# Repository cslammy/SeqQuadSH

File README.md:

# SeqQuadSH
for details please see this blog post: http://audiodiwhy.blogspot.com/2022/03/sequencial-quad-samplehold.html

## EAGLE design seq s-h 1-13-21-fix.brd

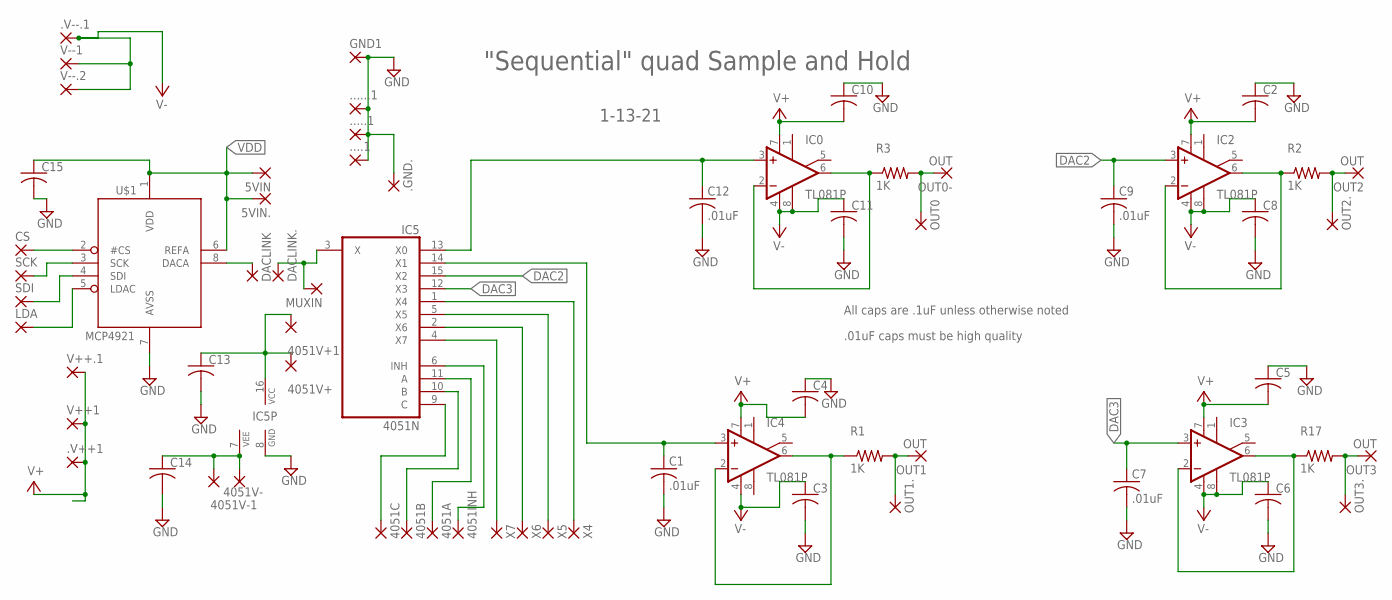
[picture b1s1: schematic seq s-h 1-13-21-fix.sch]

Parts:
5VIN: WIREPAD3,17/1,3; 3,17/1,3@1
5VIN., 4051A, 4051B, 4051C, 4051INH, 4051V+1, 4051V-1, .GND.: WIREPAD1,6/0,9; 1,6/0,9
4051V+, 4051V-, ....1, .....1, ......1, .V--.1: 3,17/1,3
.V++1: 2,54/1,0
C1, C7, C9, C12: .01uF; C050-025X075
C2, C3, C4, C5, C6, C8, C10, C11, C13, C14, C15: C-US025-024X044; C025-024X044
CS: WIREPAD1,6/0,9; 1,6/0,9
DACLINK, DACLINK.: WIREPAD1,6/0,9; 1,6/0,9
GND1: 3,17/1,3
IC0, IC2, IC3, IC4: TL081P; DIL08
IC5: 4051N; DIL16
LDA: WIREPAD1,6/0,9; 1,6/0,9
MUXIN: 3,17/1,3
OUT0, OUT1., OUT2., OUT3.: WIREPAD1,6/0,9; 1,6/0,9
OUT0-, OUT1, OUT2, OUT3: OUT; 3,17/1,3
R1, R2, R3, R17: 1K; 0204/7
SCK: WIREPAD1,6/0,9; 1,6/0,9
SDI: WIREPAD1,6/0,9; 1,6/0,9
U$1: MCP4921; DIL08
V++1, V++.1: 2,54/1,0
V--1, V--.2: 3,17/1,3
X4, X5, X6, X7: WIREPAD1,6/0,9; 1,6/0,9

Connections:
DAC2: C9.1, IC2.3 (+IN), IC5.15 (X2)
DAC3: C7.1, IC3.3 (+IN), IC5.12 (X3)
GND: ....1.1, .....1.1, ......1.1, .GND..1, C1.2, C2.1, C3.2, C4.1, C5.1, C6.2, C7.2, C8.2, C9.2, C10.1, C11.2, C12.2, C13.2, C14.2, C15.2, GND1.1, IC5.8 (GND), U$1.7 (AVSS)
unnamed: OUT1.1, OUT1..1, R1.2
unnamed: DACLINK..1, IC5.3 (X), MUXIN.1
unnamed: C1.1, IC4.3 (+IN), IC5.14 (X1)
unnamed: OUT2.1, OUT2..1, R2.2
unnamed: IC4.2 (-IN), IC4.6 (OUT), R1.1
unnamed: IC2.2 (-IN), IC2.6 (OUT), R2.1
unnamed: CS.1, U$1.2 (#CS)
unnamed: OUT0.1, OUT0-.1, R3.2
unnamed: IC0.2 (-IN), IC0.6 (OUT), R3.1
unnamed: C12.1, IC0.3 (+IN), IC5.13 (X0)
unnamed: SCK.1, U$1.3 (SCK)
unnamed: SDI.1, U$1.4 (SDI)
unnamed: LDA.1, U$1.5 (LDAC)
unnamed: 4051C.1, IC5.9 (C)
unnamed: 4051B.1, IC5.10 (B)
unnamed: 4051A.1, IC5.11 (A)
unnamed: 4051INH.1, IC5.6 (INH)
unnamed: IC3.2 (-IN), IC3.6 (OUT), R17.1
unnamed: OUT3.1, OUT3..1, R17.2
unnamed: IC5.4 (X7), X7.1
unnamed: IC5.2 (X6), X6.1
unnamed: IC5.5 (X5), X5.1
unnamed: IC5.1 (X4), X4.1
unnamed: 4051V+.1, 4051V+1.1, C13.1, IC5.16 (VCC)
unnamed: 4051V-.1, 4051V-1.1, C14.1, IC5.7 (VEE)
unnamed: DACLINK.1, U$1.8 (DACA)
V+: .V++1.1, C2.2, C4.2, C5.2, C10.2, IC0.7 (V+), IC2.7 (V+), IC3.7 (V+), IC4.7 (V+), V++1.1, V++.1.1
V-: .V--.1.1, C3.1, C6.1, C8.1, C11.1, IC0.4 (V-), IC0.8 (OPT), IC2.4 (V-), IC2.8 (OPT), IC3.4 (V-), IC3.8 (OPT), IC4.4 (V-), V--1.1, V--.2.1
VDD: 5VIN.1, 5VIN..1, C15.1, U$1.1 (VDD), U$1.6 (REFA)

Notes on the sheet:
"Sequential" quad Sample and Hold
1-13-21
All caps are .1uF unless otherwise noted
.01uF caps must be high quality

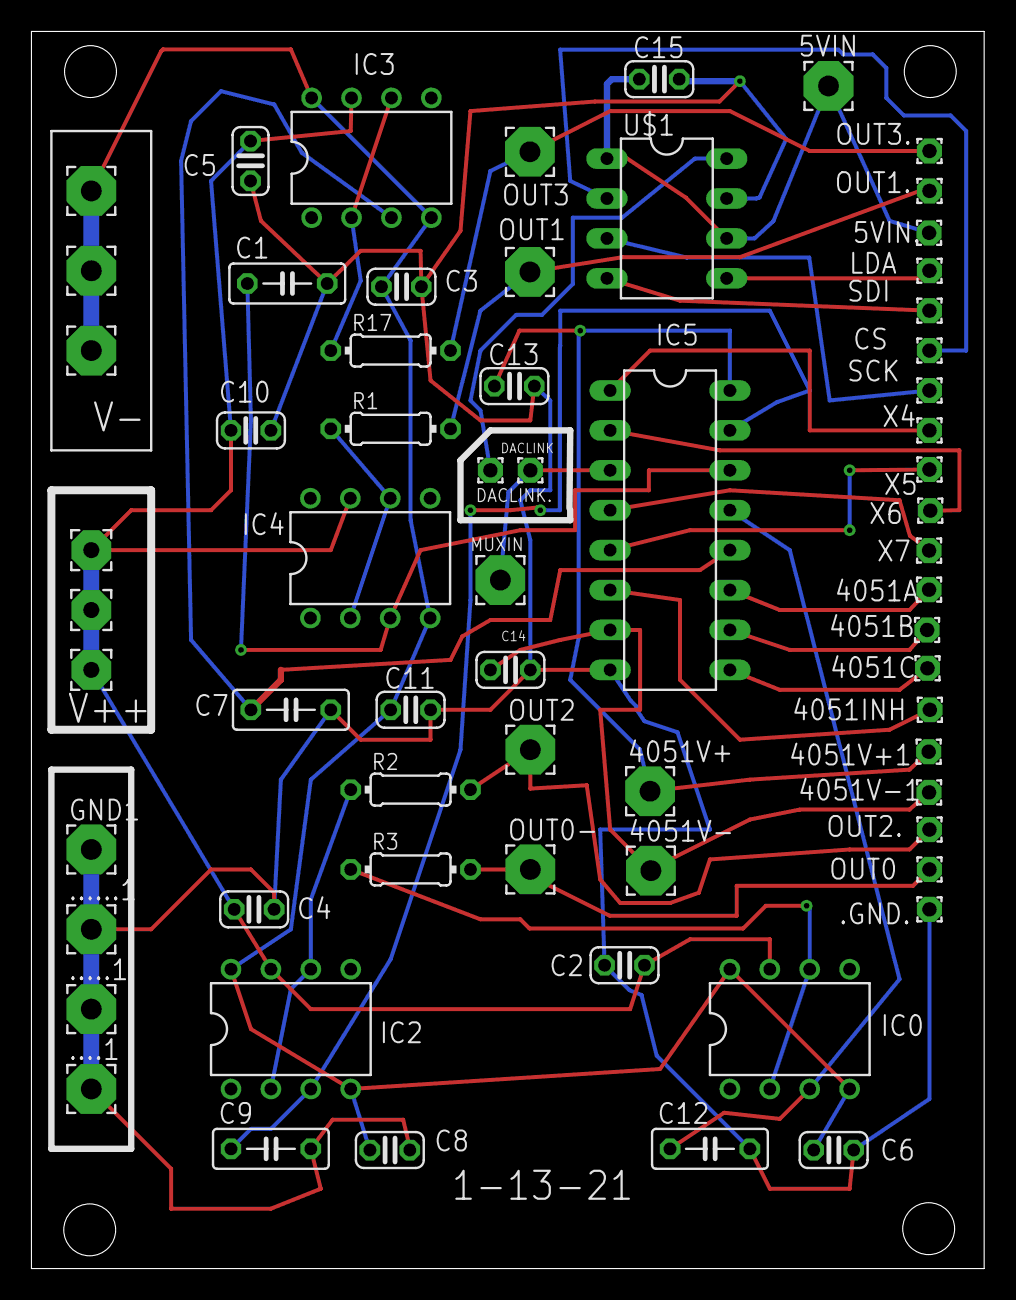
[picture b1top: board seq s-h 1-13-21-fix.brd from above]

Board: 2 copper layers, 60.6 x 78.7 mm, 65 parts (0 on the bottom side), 32 nets.

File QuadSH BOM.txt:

BOM for Seq SH

Part     Value   Device          Package      Description                  POPULARITY SPICEPREFIX
                                  
                     
                                    
                  
C1       .01uF   C-US050-025X075 C050-025X075 CAPACITOR, American symbol   0          C          
C2               C-US025-024X044 C025-024X044 CAPACITOR, American symbol   17         C          
C3               C-US025-024X044 C025-024X044 CAPACITOR, American symbol   17         C          
C4               C-US025-024X044 C025-024X044 CAPACITOR, American symbol   17         C          
C5               C-US025-024X044 C025-024X044 CAPACITOR, American symbol   17         C          
C6               C-US025-024X044 C025-024X044 CAPACITOR, American symbol   17         C          
C7       .01uF   C-US050-025X075 C050-025X075 CAPACITOR, American symbol   0          C          
C8               C-US025-024X044 C025-024X044 CAPACITOR, American symbol   17         C          
C9       .01uF   C-US050-025X075 C050-025X075 CAPACITOR, American symbol   0          C          
C10              C-US025-024X044 C025-024X044 CAPACITOR, American symbol   17         C          
C11              C-US025-024X044 C025-024X044 CAPACITOR, American symbol   17         C          
C12      .01uF   C-US050-025X075 C050-025X075 CAPACITOR, American symbol   0          C          
C13              C-US025-024X044 C025-024X044 CAPACITOR, American symbol   17         C          
C14              C-US025-024X044 C025-024X044 CAPACITOR, American symbol   17         C          
C15              C-US025-024X044 C025-024X044 CAPACITOR, American symbol   17         C          
                     
                                  
IC0      TL081P  TL081P          DIL08        OP AMP  // 071 or 061 should work as well.                                           
IC2      TL081P  TL081P          DIL08        OP AMP                                             
IC3      TL081P  TL081P          DIL08        OP AMP                                             
IC4      TL081P  TL081P          DIL08        OP AMP                                             
IC5      4051N   4051N           DIL16        8-channel ANALOG MULTIPLEXER 15                    
                                
OUT3.            WIREPAD1,6/0,9  1,6/0,9      Wire PAD connect wire on PCB 0                     
R1       1K      R-US_0204/7     0204/7       RESISTOR, American symbol                          
R2       1K      R-US_0204/7     0204/7       RESISTOR, American symbol                          
R3       1K      R-US_0204/7     0204/7       RESISTOR, American symbol                          
R17      1K      R-US_0204/7     0204/7       RESISTOR, American symbol                          
                    
U$1      MCP4921 MCP4921         DIL08                                                           
 
C1`, C7, C9, and C12 should be high quality caps--mylar, poly, etc.
All other caps are .1uF.

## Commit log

2022-03-06 Atmel Studio 7 code
2022-03-06 initial upload
    Initial BOM, brd, sch, gerber, and PDF of layout and schematic.
